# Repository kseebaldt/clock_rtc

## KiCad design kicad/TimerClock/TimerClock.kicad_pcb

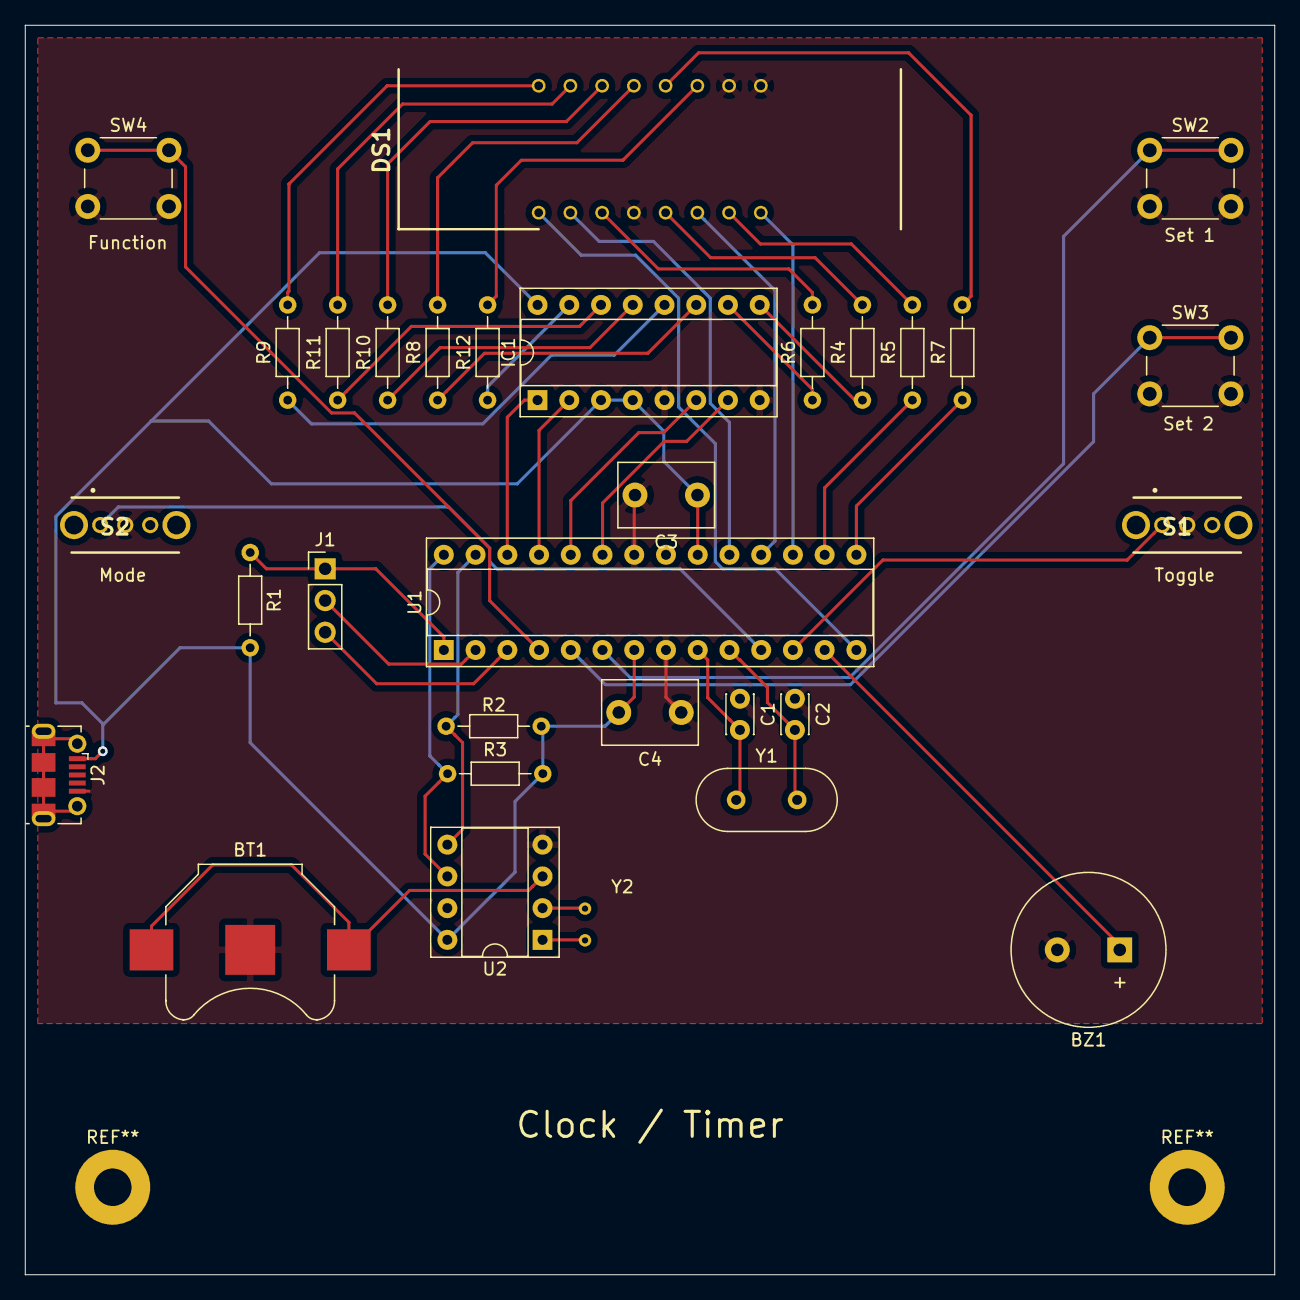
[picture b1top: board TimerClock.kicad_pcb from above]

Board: 2 copper layers, 100.0 x 100.0 mm, 31 parts (1 on the bottom side), 44 nets.

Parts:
BT1: Battery_Cell; BatteryHolder_Keystone_3000_1x12mm
BZ1: Buzzer; Buzzer_12x9.5RM5.0
C1, C2: 22pF; C_Disc_D3.0mm_W2.0mm_P2.50mm
C3, C4: 0.1uF; C_Disc_D7.5mm_W5.0mm_P5.00mm
DS1: TDCG1060M; DIPS1016W50P254L4020H700Q16N
IC1: CD4511BE; DIP-16_W7.62mm_Socket
J1: Conn_01x03; PinHeader_1x03_P2.54mm_Vertical
J2: USB_B_Micro; USB_Micro-B_Molex-105017-0001
R1: 10k; R_Axial_DIN0204_L3.6mm_D1.6mm_P7.62mm_Horizontal
R2, R3: 2.2k; R_Axial_DIN0204_L3.6mm_D1.6mm_P7.62mm_Horizontal
R4, R5, R6, R8, R9, R10, R11, R12: 220; R_Axial_DIN0204_L3.6mm_D1.6mm_P7.62mm_Horizontal
R7: 1k; R_Axial_DIN0204_L3.6mm_D1.6mm_P7.62mm_Horizontal
S1, S2: OS102011MS2QN1; OS102011MA1QN1
SW2, SW3, SW4: SW_Push; SW_PUSH_6mm
U1: ATmega328P-PU; DIP-28_W7.62mm_Socket
U2: DS1307+; DIP-8_W7.62mm_Socket
Y1: 16MHz; Crystal_HC49-U_Vertical
Y2: 32KHz; Crystal_AT310_D3.0mm_L10.0mm_Horizontal

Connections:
/A0: IC1.7, U1.23
/A1: IC1.6, U1.24
/A2: IC1.2, U1.25
/A3: IC1.1, U1.26
/A4: R2.2, U1.27, U2.5
/A5: R3.1, U1.28, U2.6
/D2: SW4.1, U1.4
/D3: SW3.1, U1.5
/D4: SW2.1, U1.6
/D5: S2.1, U1.11
/D6: S1.1, U1.12
/D7: BZ1.1, U1.13
/D8: DS1.1, U1.14
/D9: R7.1, U1.15
/D10: R5.1, U1.16
/D11: DS1.8, U1.17
/D12: DS1.6, U1.18
/D13: DS1.2, U1.19
GND: BT1.2, BZ1.2, C1.1, C2.1, C3.2, C4.1, DS1.4, DS1.9, DS1.10, IC1.5, IC1.8, J2.5, S1.2, S2.2, SW2.2, SW3.2, SW4.2, U1.8, U1.22, U2.4
unnamed: BT1.1, U2.3
unnamed: C1.2, U1.9, Y1.1
unnamed: C2.2, U1.10, Y1.2
unnamed: C3.1, C4.2, IC1.3, IC1.4, IC1.16, J2.1, R1.2, R2.1, R3.2, U1.7, U1.20, U2.8
unnamed: DS1.3, R6.2
unnamed: DS1.5, R4.2
unnamed: DS1.7, R5.2
unnamed: DS1.11, R12.2
unnamed: DS1.12, R7.2
unnamed: DS1.13, R8.2
unnamed: DS1.14, R10.2
unnamed: DS1.15, R11.2
unnamed: DS1.16, R9.2
unnamed: IC1.9, R4.1
unnamed: IC1.10, R6.1
unnamed: IC1.11, R8.1
unnamed: IC1.12, R9.1
unnamed: IC1.13, R10.1
unnamed: IC1.14, R11.1
unnamed: IC1.15, R12.1
unnamed: J1.1, R1.1, U1.1
unnamed: J1.2, U1.2
unnamed: J1.3, U1.3
unnamed: U2.1, Y2.2
unnamed: U2.2, Y2.1

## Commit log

2019-05-11 BcdDriver and ArduinoWrapper for testing
2019-05-12 fix wrapper call to arduino; calculate digits correctly
2019-05-12 restructure unit tests
2019-05-12 basic Clock functionality
2019-05-13 support display modes, increment, decrement
2019-05-13 button debounce class
2019-05-13 fix library directory layout
2019-05-13 add button callbacks
2019-05-13 add callback repeat
2019-05-14 add Clock button adjustments
2019-05-14 timer on/off
2019-05-14 add clock and timer mode
2019-05-14 change pin mapping to match new schematic
2019-05-15 add display flags
2019-05-15 fix display flags
2019-05-15 add missing header file
2019-05-15 add alarm state
2019-05-15 set alarm to rtc nvram
2019-05-16 add alarm buzzer
2019-05-16 rename clock alarm callback type
2019-05-16 test timer buttons
2019-05-16 add timer alarm
2019-05-16 fix overflow setting timer
2019-05-16 do not start timer if at zero
2019-05-21 add kicad files
